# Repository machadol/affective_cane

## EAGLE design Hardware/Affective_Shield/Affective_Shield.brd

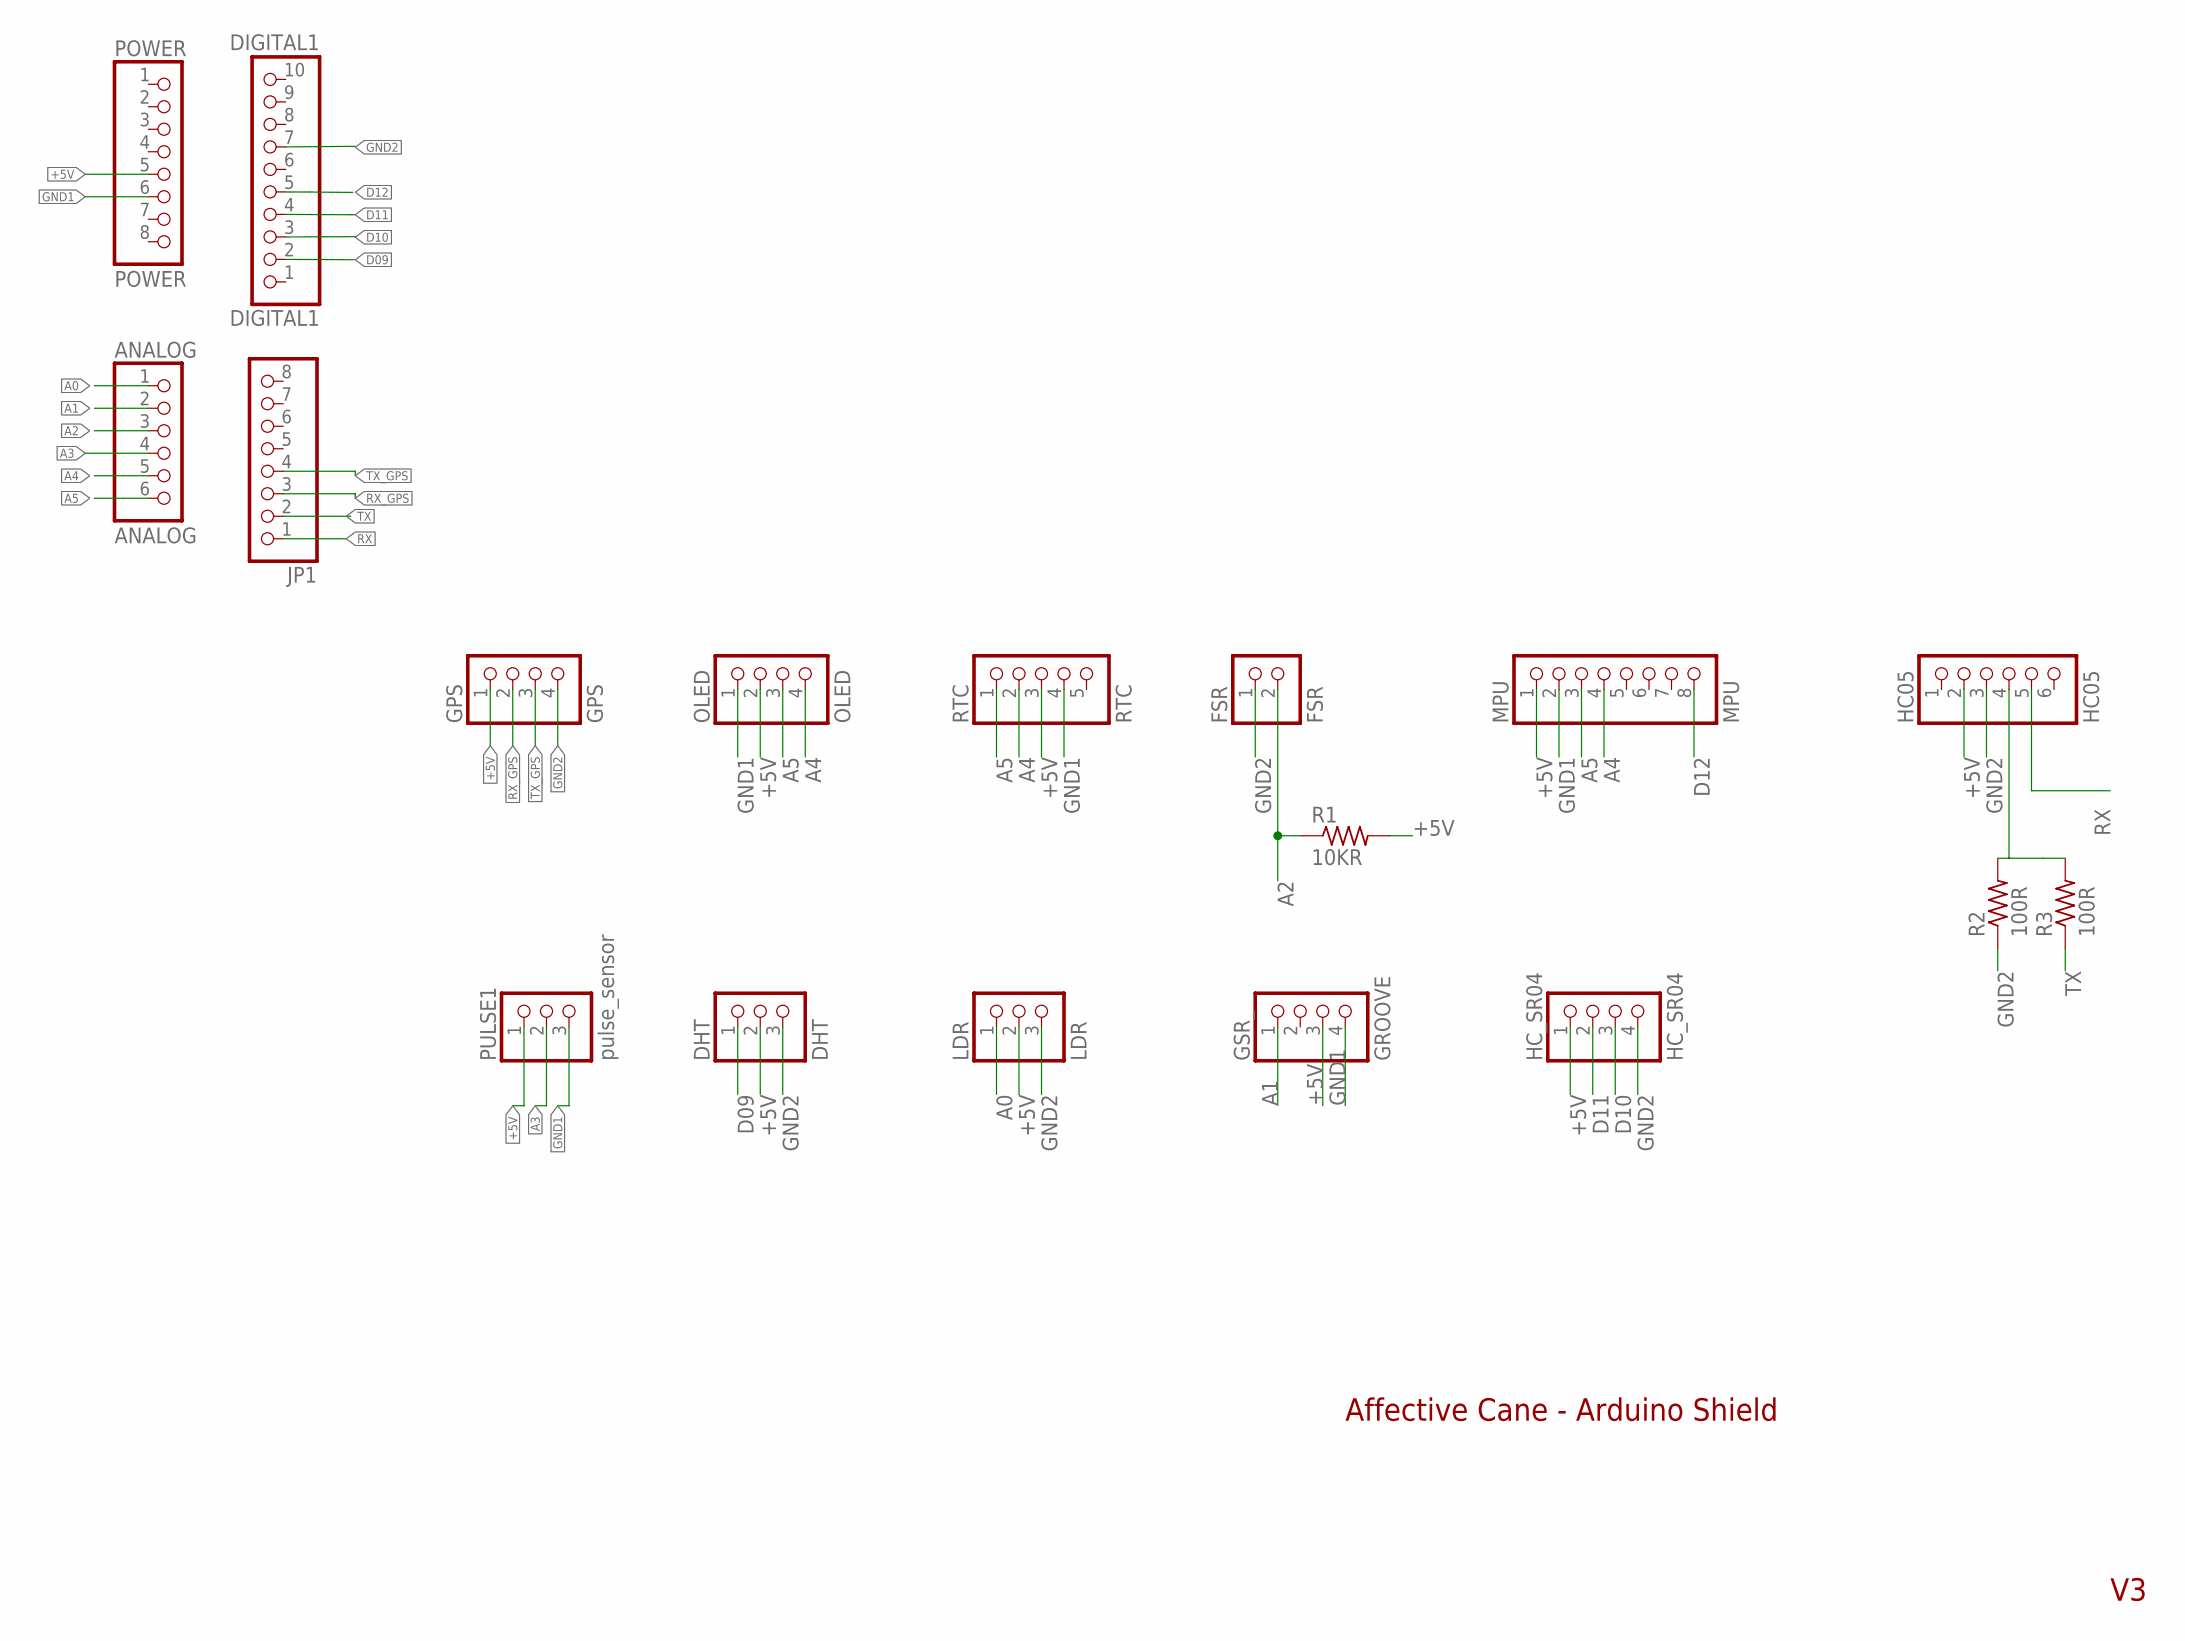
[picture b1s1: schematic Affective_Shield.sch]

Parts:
ANALOG: ANALOG; 1X06
DHT: DHT; 1X03
DIGITAL1: DIGITAL1; 1X10
FSR: FSR; 1X02
GPS: GPS; 1X04
GSR_: GROOVE; 1X04
HC05: HC05; 1X06
HC_SR04: HC_SR04; 1X04
JP1: PINHD-1X8; 1X08
LDR: LDR; 1X03
MPU: MPU; 1X08
OLED: OLED; 1X04
POWER: POWER; 1X08
PULSE1: pulse_sensor; 1X03
R1: 10KR; 0204/7
R2, R3: 100R; 0204/7
RTC: RTC; 1X05

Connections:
+5V: DHT.2, GPS.1, GSR_.3, HC05.2, HC_SR04.1, LDR.2, MPU.1, OLED.2, POWER.5, PULSE1.1, R1.2, RTC.3
A0: ANALOG.1, LDR.1
A1: ANALOG.2, GSR_.1
A2: ANALOG.3, FSR.2, R1.1
A3: ANALOG.4, PULSE1.2
A4: ANALOG.5, MPU.4, OLED.4, RTC.2
A5: ANALOG.6, MPU.3, OLED.3, RTC.1
D09: DHT.1, DIGITAL1.2
D10: DIGITAL1.3, HC_SR04.3
D11: DIGITAL1.4, HC_SR04.2
D12: DIGITAL1.5, MPU.8
GND1: GSR_.4, MPU.2, OLED.1, POWER.6, PULSE1.3, RTC.4
GND2: DHT.3, DIGITAL1.7, FSR.1, GPS.4, HC05.3, HC_SR04.4, LDR.3, R2.1
unnamed: HC05.4, R2.2, R3.2
RX: HC05.5, JP1.1
RX_GPS: GPS.2, JP1.3
TX: JP1.2, R3.1
TX_GPS: GPS.3, JP1.4

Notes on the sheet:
Affective Cane - Arduino Shield

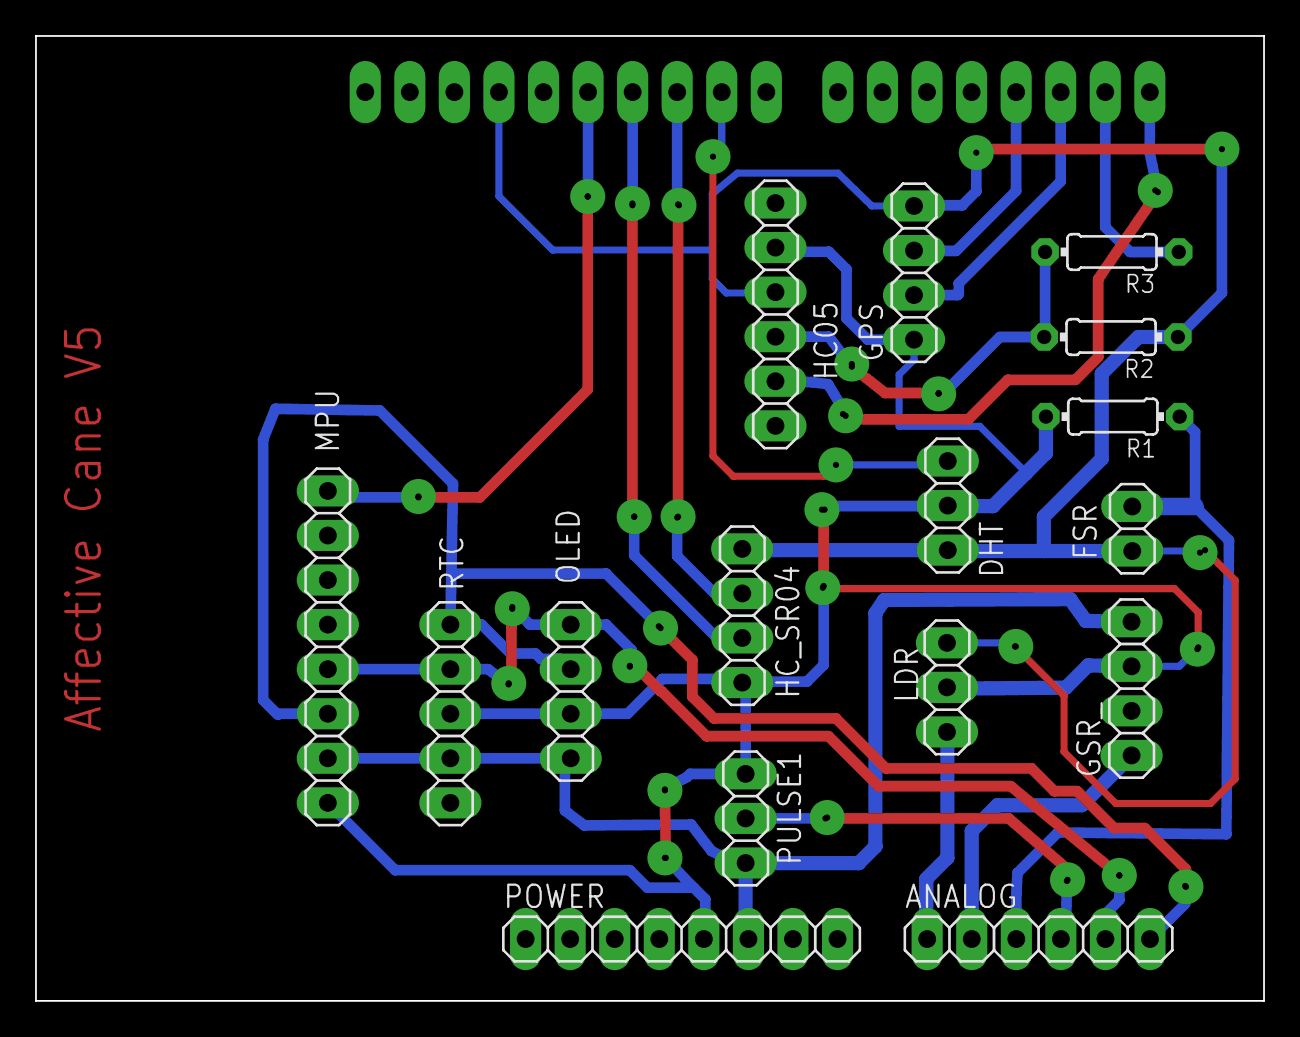
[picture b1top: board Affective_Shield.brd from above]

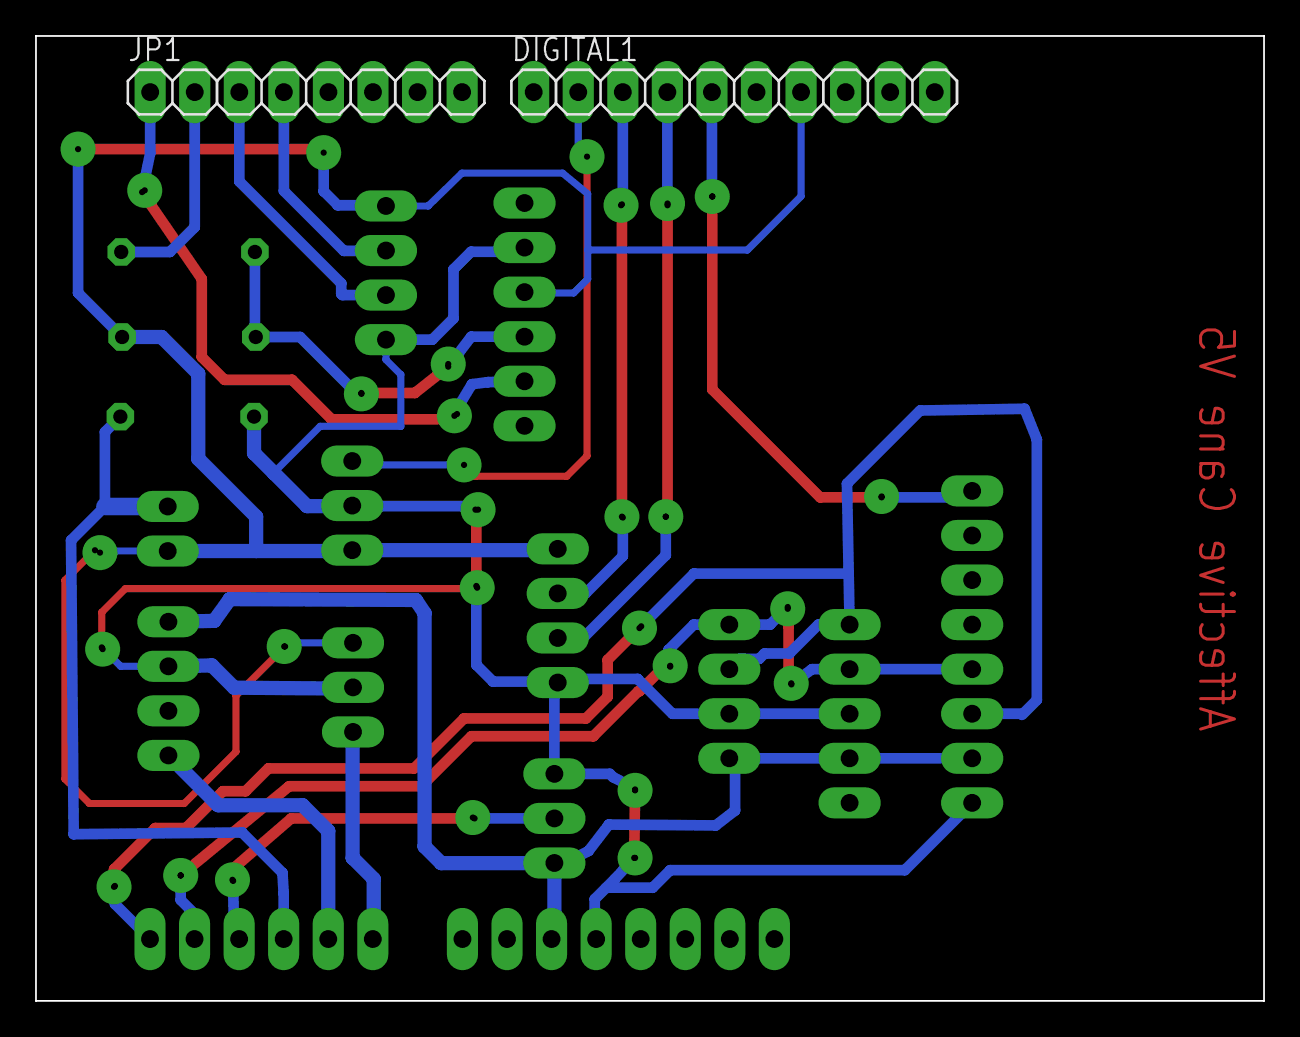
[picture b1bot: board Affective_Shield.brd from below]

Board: 2 copper layers, 70.0 x 55.0 mm, 18 parts (2 on the bottom side), 18 nets.

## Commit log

2017-10-07 Versão inicial
2017-10-07 Parâmetros aferidos
2017-10-07 Datasheet
2017-10-12 Arduino Shield V1
2017-10-13 Bluetooh corrigido (posicionamento e RX)
2017-10-13 Bluetooh corrigido (posicionamento e RX-TX)
2017-10-14 Shield corrigido
2017-10-15 Biblioteca FSR
2017-10-17 adição de pasta Examples e Bibliotecas
    Criação de pasta com bibliotecas oficiais,
    Criação de pasta de exemplo,
    Criação de exemplo de FSR
2017-10-17 Simplificação e padronização da biblioteca
    Mudança de nomes dos métodos para aderir ao novo padrão.
2017-10-17 Criação de Exemplo da biblioteca de FSR
    Criação de código para teste do FSR. A biblioteca deve ser adicionada manualmente para o teste.
2017-10-18 Correção na biblioteca
2017-10-18 Correções estéticas no código principal do exemplo.
2017-10-18 Criação de Exemplo de funcionamento de IMU + FSR
2017-10-18 Criação de exemplo de Biblioteca de timer
2017-10-18 Criação de Exemplo de visualização.
2017-10-19 Adiçao de exemplos e biblioteca de Thermistores.
2017-10-20 Acréscimo do DHT
2017-10-20 Adição de exemplos e biblioteca do LDR e DHT22
2017-10-20 LDR, DHT e Termistor implementados
2017-10-23 Added floor and rotating square
2017-10-24 Visualization V2.0 first Commit
    Added new visualization with some features:
    - Ground effect
    - Changing block color
    - Changing background effects
2017-10-25 Visualization V2.0 enhancements
    - Better color distribution
    - Included method for background color.
2017-10-25 V2.0 file writer improvements
    - Log of the test session is being recorded in the Data folder of the processing sketch
2017-10-25 V2.0 FSR data decoding
2017-10-25 V2.0 enhancements
    Connection of the FSR in the visualization
2017-10-25 V2.0 enhancements in floor and fsr
    -floor is changing with FSRStatus
2017-10-25 aaaa
2017-10-27 Integração Bengala Processing
    Exemplo de import de STL
2017-10-27 V2.0 with new design (cylindrical Cane)
    This version substituted the cube by a stylized version of the cane.
2017-10-27 Complementing the 2.0 Cylindrical release
2017-12-06 Change the colors in the Btemp with map
2017-12-14 Adição de exemplos e biblioteca (Termistor e Ultrasônico)
2017-12-14 Versão 3 - Faltando revisão
2018-05-08 create a new controller
2018-05-14 Add Oximetry and GPS
    Oximetry sensor added. GPS added
2018-05-14 Brd schematics
2018-05-18 Add main Fw
2018-05-19 Add GPS support (Now Correctly)
2018-05-19 Added Accelerometer Support
2018-05-19 Add support to OLED display
2018-05-22 calcular o tempo de recebimento de informações em milisegundos
2018-05-22 calcular o tempo de recebimento de informações em segundos
2018-05-23 deixar em loop até esr finalizada a instrução
2018-05-24 melhorar o tempo de amostragem para milisegundos
2018-05-25 save in file the datas and open the serial port
2018-05-25 add the method to create and read the file and change the form of input
2018-05-25 add method save_data_two_inputs
2018-05-26 creat the method to save more than one data in some files
2018-05-29 Add last version
2018-05-30 shield corrective update: Changed some ports, and adapted to only bottom solder on components
2018-05-30 minor changes to sync HW and FW
2018-05-30 add examples
2018-06-16 Minor correction - Inverting Bluetooth pins in the board
2018-06-16 Adding button to count time for power down
2018-06-17 Enhancement of Accelerometer readings
2018-06-22 improvement to protocol and refresh rates
2018-09-05 Added a codifier of int, float and array of ints
2018-09-14 Adding new RT visualizer
2018-09-14 Adding the last Arduino visualizer FW to repo
2018-09-15 separing the Serial port from code
2018-09-18 Adding Threaded add to watcher
2018-09-20 Added support to Ambiental and Touch sensors
2018-09-20 Mudanças no software completo de arduino para suporte do Toque, e temperatura umidade rapidas
